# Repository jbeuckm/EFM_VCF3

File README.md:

# EFM_VCF3
http://electro-music.com/forum/phpbb-files/wildcat_001_20_518.jpg

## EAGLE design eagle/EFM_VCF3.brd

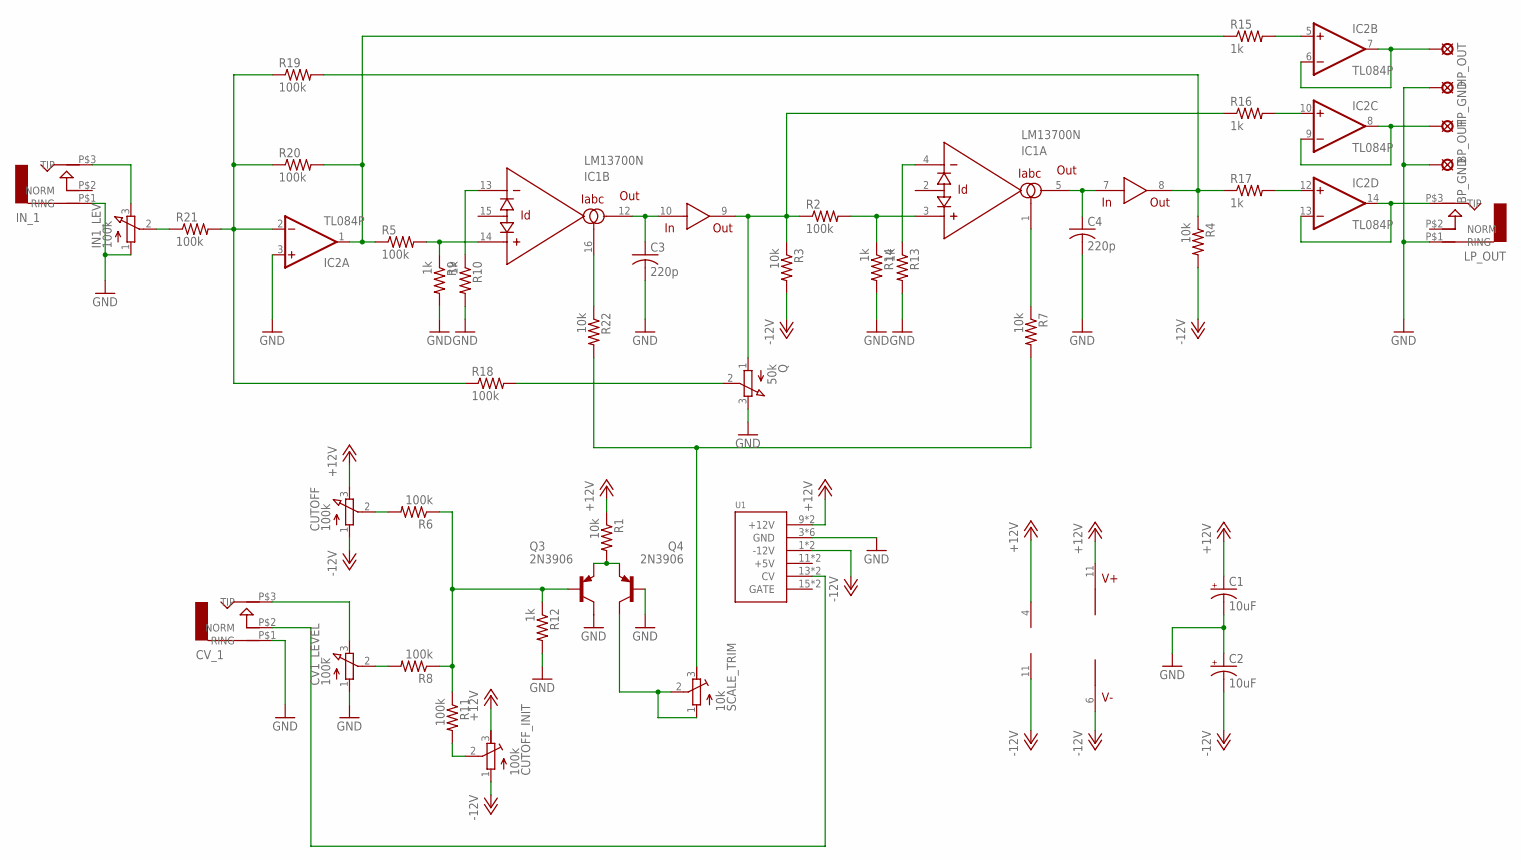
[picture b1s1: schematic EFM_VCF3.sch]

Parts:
BP_GND: LSP10
BP_OUT: LSP10
C1, C2: 10uF; B45181A
C3, C4: 220p; C075-032X103
CUTOFF: 100k; 3RP/1610N
CUTOFF_INIT: 100k; RTRIM64W
CV1_LEVEL: 100k; 3RP/1610N
CV_1: AUDIO-JACK; ERTHENVAR-JACK-90DEG
HP_GND: LSP10
HP_OUT: LSP10
IC1: LM13700N; DIL16
IC2: TL084P; DIL14
IN1_LEV: 100k; 3RP/1610N
IN_1: AUDIO-JACK; ERTHENVAR-JACK-90DEG
LP_OUT: AUDIO-JACK; ERTHENVAR-JACK-90DEG
Q: 50k; 3RP/1610N
Q3, Q4: 2N3906; TO92
R1, R3, R4, R7: 10k; 0207/7
R2, R5, R6, R8, R11, R18, R19, R20, R21: 100k; 0207/7
R9, R10, R12, R13, R14, R15, R16, R17: 1k; 0207/7
R22: 10k; 0309/10
SCALE_TRIM: 10k; RTRIM64W
U1: POWER; POWER_16

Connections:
+12V: C1.+, CUTOFF.3 (E), CUTOFF_INIT.3 (E), IC1.11 (V+), IC2.4 (V+), R1.1, U1.9 (+12V), U1.10 (+12V)
-12V: C2.-, CUTOFF.1 (A), CUTOFF_INIT.1 (A), IC1.6 (V-), IC2.11 (V-), R3.2, R4.2, U1.1 (-12V), U1.2 (-12V)
GND: BP_GND.MP, C1.-, C2.+, C3.2, C4.2, CV1_LEVEL.1 (A), CV_1.P$1 (RING), HP_GND.MP, IC2.3 (+IN), IN1_LEV.1 (A), IN_1.P$1 (RING), LP_OUT.P$1 (RING), Q.3 (E), Q3.1 (C), Q4.2 (B), R9.2, R10.2, R12.2, R13.2, R14.2, U1.3 (GND), U1.4 (GND), U1.5 (GND), U1.6 (GND), U1.7 (GND), U1.8 (GND)
unnamed: Q3.3 (E), Q4.3 (E), R1.2
unnamed: C3.1, IC1.10 (IN), IC1.12 (OUT)
unnamed: C4.1, IC1.5 (OUT), IC1.7 (IN)
unnamed: IC1.14 (+IN), R5.2, R9.1
unnamed: IC1.9 (OUT), Q.1 (A), R2.1, R3.1, R16.1
unnamed: IC1.3 (+IN), R2.2, R14.1
unnamed: IC1.13 (-IN), R10.1
unnamed: IC1.4 (-IN), R13.1
unnamed: IC2.1 (OUT), R5.1, R15.1, R20.2
unnamed: CV1_LEVEL.2 (S), R8.2
unnamed: IC2.5 (+IN), R15.2
unnamed: IC2.10 (+IN), R16.2
unnamed: IC2.12 (+IN), R17.2
unnamed: IC2.13 (-IN), IC2.14 (OUT), LP_OUT.P$3 (TIP)
unnamed: BP_OUT.MP, IC2.8 (OUT), IC2.9 (-IN)
unnamed: IC1.1 (IABC), R7.1
unnamed: HP_OUT.MP, IC2.6 (-IN), IC2.7 (OUT)
unnamed: Q3.2 (B), R6.1, R8.1, R11.1, R12.1
unnamed: Q.2 (S), R18.2
unnamed: IC1.16 (IABC), R22.1
unnamed: R7.2, R22.2, SCALE_TRIM.3 (E)
unnamed: IN1_LEV.3 (E), IN_1.P$3 (TIP)
unnamed: IC1.8 (OUT), R4.1, R17.1, R19.2
unnamed: IN1_LEV.2 (S), R21.1
unnamed: Q4.1 (C), SCALE_TRIM.1 (A), SCALE_TRIM.2 (S)
unnamed: IC2.2 (-IN), R18.1, R19.1, R20.1, R21.2
unnamed: CUTOFF_INIT.2 (S), R11.2
unnamed: CV1_LEVEL.3 (E), CV_1.P$3 (TIP)
unnamed: CV_1.P$2 (NORM), U1.13 (CV), U1.14 (CV)
unnamed: CUTOFF.2 (S), R6.2

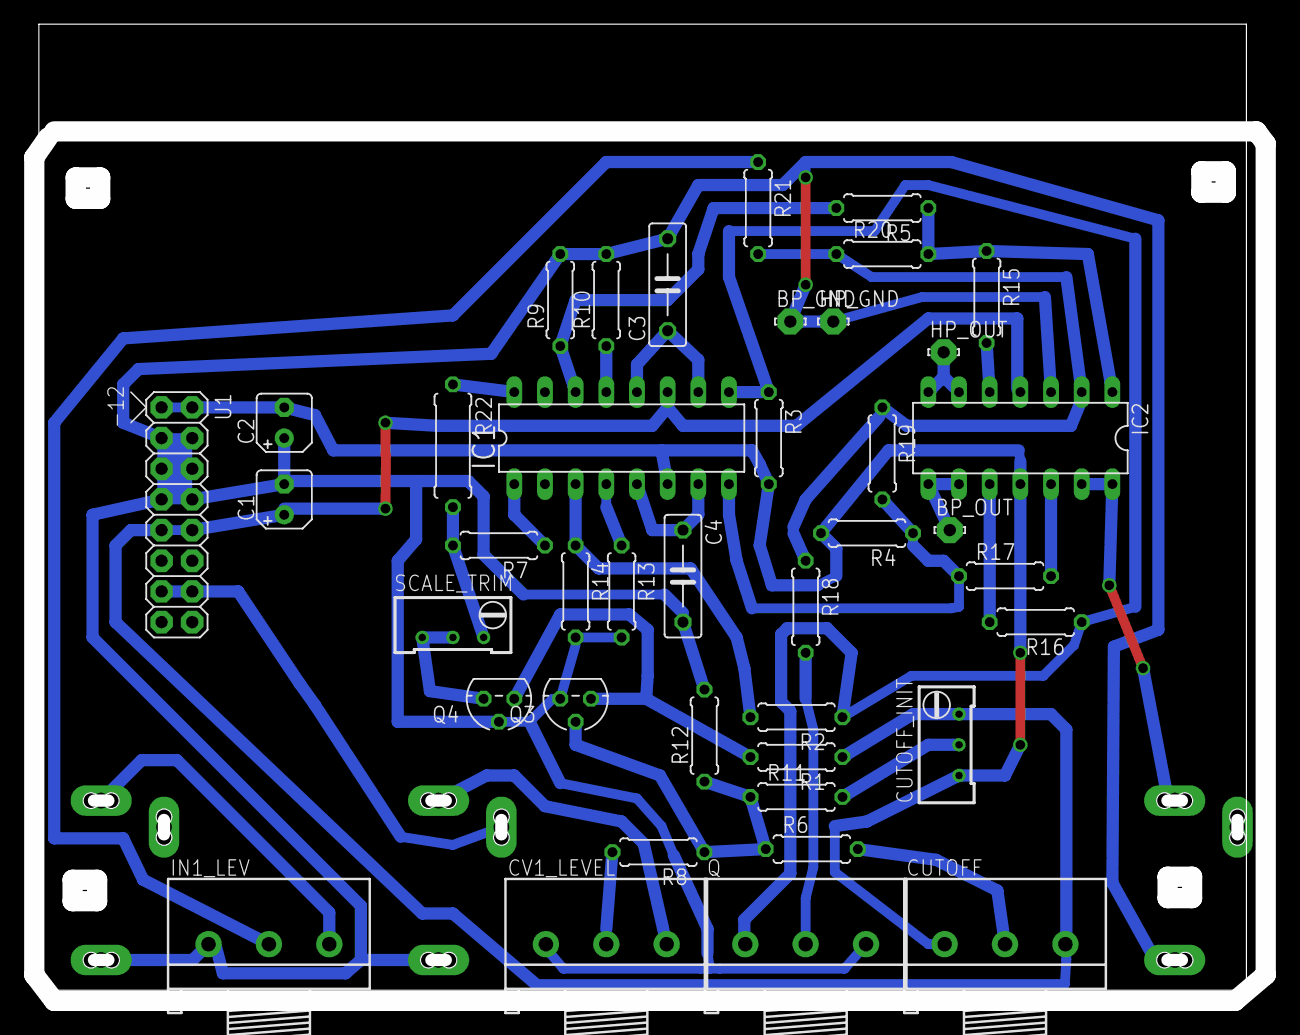
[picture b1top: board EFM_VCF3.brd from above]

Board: 2 copper layers, 102.0 x 80.1 mm, 44 parts (0 on the bottom side), 33 nets.

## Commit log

2015-12-02 more parts
2015-12-02 parts in place
2015-12-02 started the board
2015-12-02 working on brd
2015-12-03 almost routed
2015-12-03 gcode
2015-12-04 fixed connections
2015-12-04 tweaked
2015-12-07 fixed resonance direction
2015-12-07 tweaks and one less jump
2016-01-22 ready to try fixed res cut
2016-10-25 gcode for rectangular cut
2018-01-24 update layout and add 3d printed panel
